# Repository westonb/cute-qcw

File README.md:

# cute-qcw
A compact qcw tesla coil system with a FPGA based controller. System design and construction are in progress. Build photos viewable here: https://www.flickr.com/photos/63341195@N08/sets/72157678478822788/

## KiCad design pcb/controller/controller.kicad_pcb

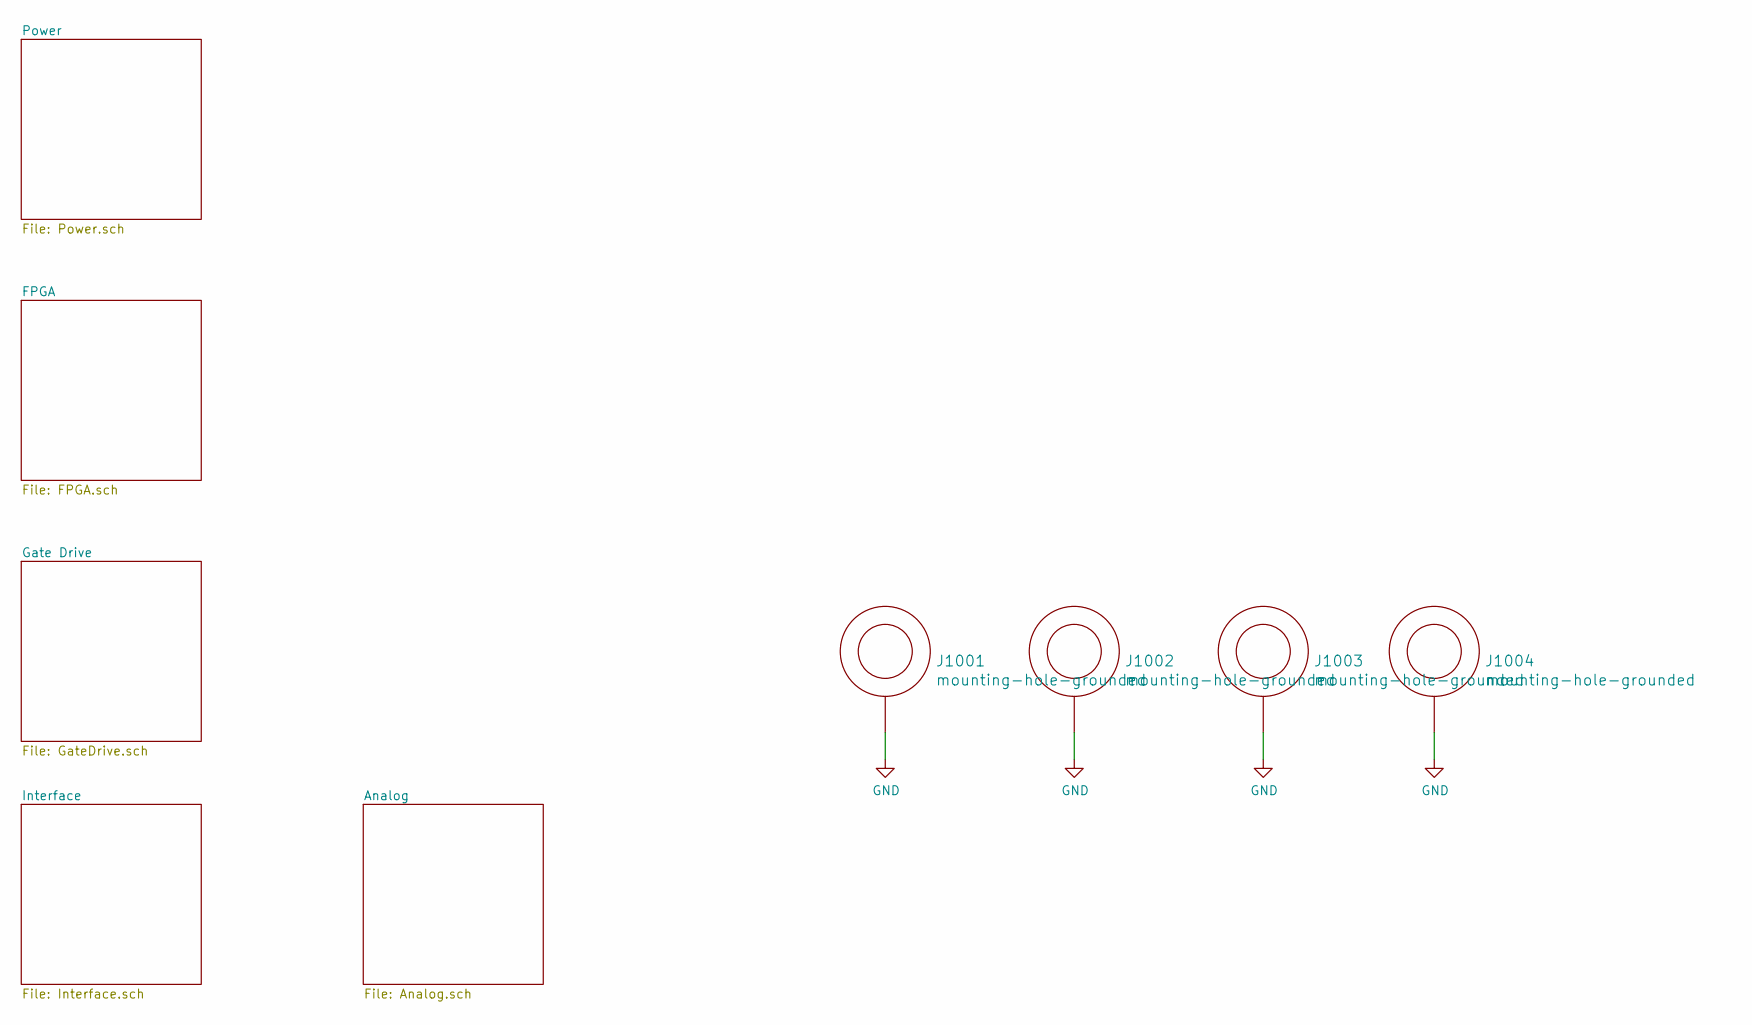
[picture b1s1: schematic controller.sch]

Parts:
J1001, J1002, J1003, J1004: mounting-hole-grounded; M3-tight-fit-pan-head

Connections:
GND: J1001.1, J1002.1, J1003.1, J1004.1; also elsewhere on the board

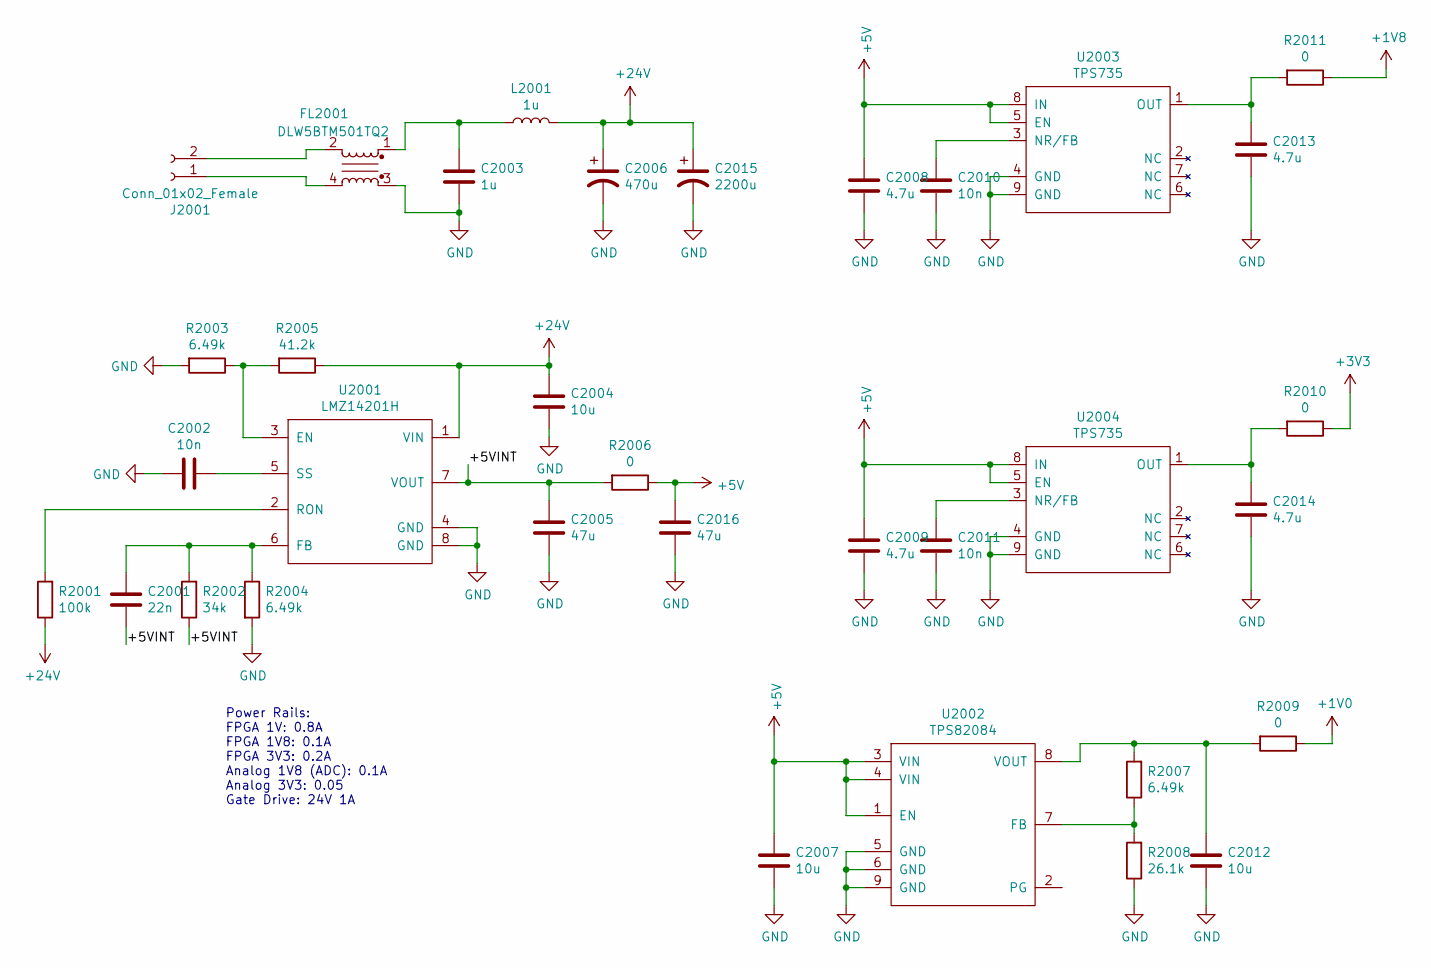
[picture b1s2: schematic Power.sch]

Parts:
C2001: 22n; C_0402_1005Metric
C2002, C2010, C2011: 10n; C_0402_1005Metric
C2003: 1u; C_0805_2012Metric
C2004: 10u; C_1206_3216Metric
C2005, C2016: 47u; C_0805_2012Metric
C2006: 470u; CP_Radial_D10.0mm_P5.00mm
C2007, C2012: 10u; C_0805_2012Metric
C2008, C2009, C2013, C2014: 4.7u; C_0402_1005Metric
C2015: 2200u; CAP_16mmx37mm_horizontal
FL2001: DLW5BTM501TQ2; DLW5BTM
J2001: Conn_01x02_Female; Terminal-block-plug_2x1_3.5mm-pitch
L2001: 1u; L_Vishay_IHLP-1212
R2001: 100k; R_0402_1005Metric
R2002: 34k; R_0402_1005Metric
R2003, R2004, R2007: 6.49k; R_0402_1005Metric
R2005: 41.2k; R_0402_1005Metric
R2006, R2009, R2010, R2011: 0; R_0805_2012Metric
R2008: 26.1k; R_0402_1005Metric
U2001: LMZ14201H; TO-PMOD-7
U2002: TPS82084; uSil-8
U2003, U2004: TPS735; SON-8_EP

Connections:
+1V0: R2009.1; also elsewhere on the board
+1V8: R2011.1; also elsewhere on the board
+3V3: R2010.1; also elsewhere on the board
+5V: C2007.1, C2008.2, C2009.2, C2016.1, R2006.1, U2002.1 (EN), U2002.3 (VIN), U2002.4 (VIN), U2003.5 (EN), U2003.8 (IN), U2004.5 (EN), U2004.8 (IN); also elsewhere on the board
+24V: C2004.1, C2006.1, C2015.1, L2001.2, R2001.1, R2005.1, U2001.1 (VIN); also elsewhere on the board
/Power/+5VINT: C2001.1, C2005.1, R2002.1, R2006.2, U2001.7 (VOUT)
GND: C2002.2, C2003.2, C2004.2, C2005.2, C2006.2, C2007.2, C2008.1, C2009.1, C2010.1, C2011.1, C2012.2, C2013.1, C2014.1, C2015.2, C2016.2, FL2001.3, R2003.2, R2004.2, R2008.1, U2001.4 (GND), U2001.8 (GND), U2002.5 (GND), U2002.6 (GND), U2002.9 (GND), U2003.4 (GND), U2003.9 (GND), U2004.4 (GND), U2004.9 (GND); also elsewhere on the board
unnamed: C2001.2, R2002.2, R2004.1, U2001.6 (FB)
unnamed: C2002.1, U2001.5 (SS)
unnamed: C2003.1, FL2001.1, L2001.1
unnamed: C2010.2, U2003.3 (NR/FB)
unnamed: C2011.2, U2004.3 (NR/FB)
unnamed: C2012.1, R2007.2, R2009.2, U2002.8 (VOUT)
unnamed: C2013.2, R2011.2, U2003.1 (OUT)
unnamed: C2014.2, R2010.2, U2004.1 (OUT)
unnamed: FL2001.2, J2001.2
unnamed: FL2001.4, J2001.1
unnamed: R2001.2, U2001.2 (RON)
unnamed: R2003.1, R2005.2, U2001.3 (EN)
unnamed: R2007.1, R2008.2, U2002.7 (FB)

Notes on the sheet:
Power Rails: FPGA 1V: 0.8A FPGA 1V8: 0.1A FPGA 3V3: 0.2A Analog 1V8 (ADC): 0.1A Analog 3V3: 0.05 Gate Drive: 24V 1A

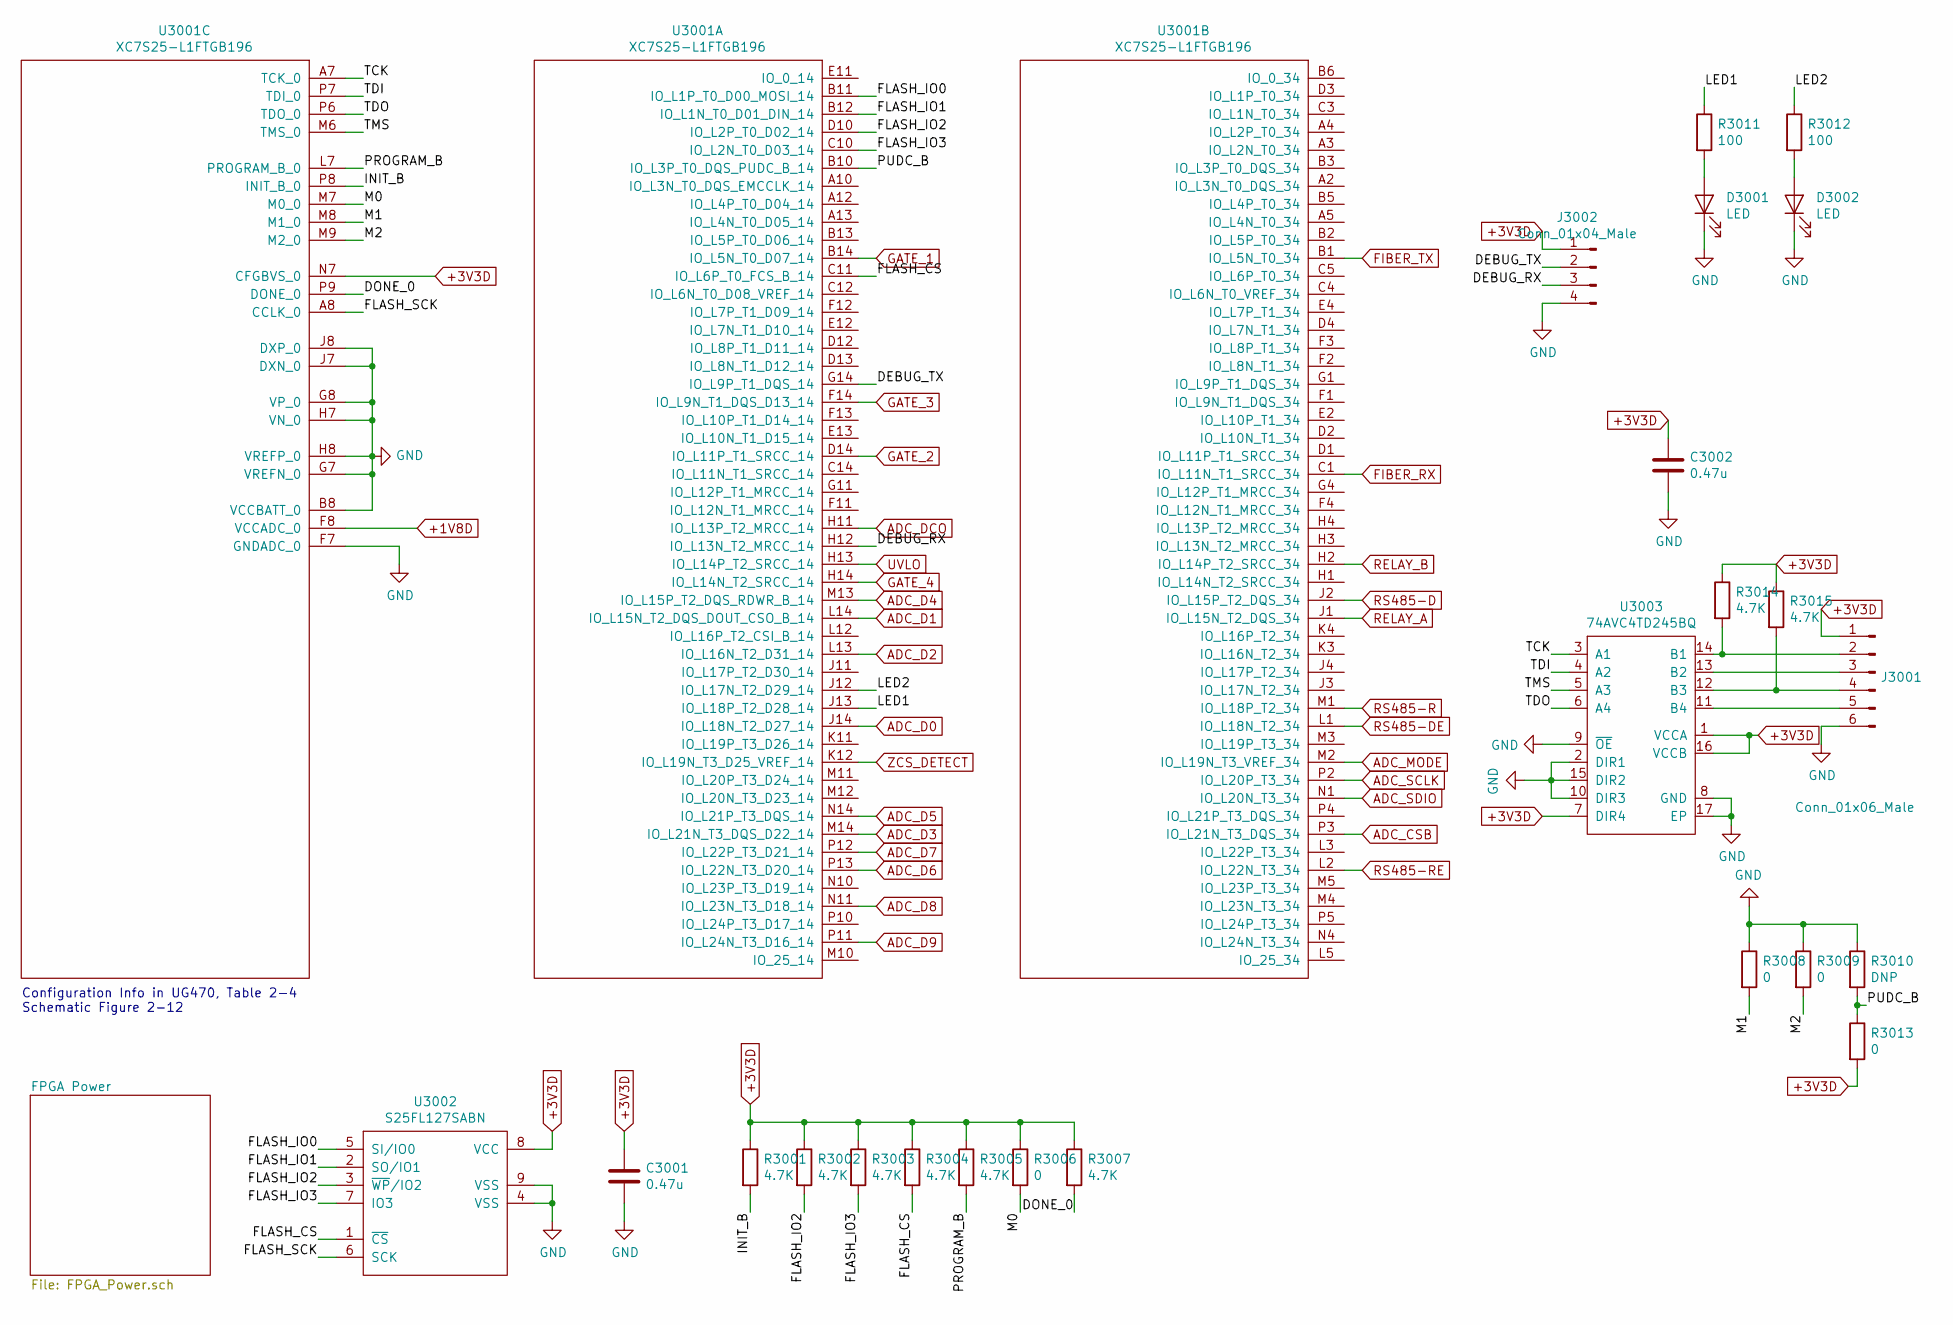
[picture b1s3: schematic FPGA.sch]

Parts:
C3001, C3002: 0.47u; C_0402_1005Metric
D3001, D3002: LED; LED-T1-RIGHT-ANGLE_4.6x4.4mm
J3001: Conn_01x06_Male; PinHeader_1x06_P2.54mm_Vertical
J3002: Conn_01x04_Male; PinHeader_1x04_P2.54mm_Vertical
R3001, R3002, R3003, R3004, R3005, R3007, R3014, R3015: 4.7K; R_0402_1005Metric
R3006, R3008, R3009, R3013: 0; R_0402_1005Metric
R3010: DNP; R_0402_1005Metric
R3011, R3012: 100; R_0402_1005Metric
U3001: XC7S25-L1FTGB196; FTGB196
U3002: S25FL127SABN; WSON-8-1EP_6x5mm_P1.27mm_EP3.4x4mm
U3003: 74AVC4TD245BQ; DHVQFN16

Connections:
+1V8D: U3001.F8 (VCCADC_0); also elsewhere on the board
+3V3D: C3001.1, C3002.1, J3001.1, J3002.1, R3001.1, R3002.1, R3003.1, R3004.1, R3005.1, R3006.1, R3007.1, R3013.2, R3014.1, R3015.1, U3001.N7 (CFGBVS_0), U3002.8 (VCC), U3003.1 (VCCA), U3003.7 (DIR4), U3003.16 (VCCB); also elsewhere on the board
/FPGA/DEBUG_RX: J3002.3, U3001.H12 (IO_L13N_T2_MRCC_14)
/FPGA/DEBUG_TX: J3002.2, U3001.G14 (IO_L9P_T1_DQS_14)
/FPGA/DONE_0: R3007.2, U3001.P9 (DONE_0)
/FPGA/FLASH_CS: R3004.2, U3001.C11 (IO_L6P_T0_FCS_B_14), U3002.1 (~CS)
/FPGA/FLASH_IO0: U3001.B11 (IO_L1P_T0_D00_MOSI_14), U3002.5 (SI/IO0)
/FPGA/FLASH_IO1: U3001.B12 (IO_L1N_T0_D01_DIN_14), U3002.2 (SO/IO1)
/FPGA/FLASH_IO2: R3002.2, U3001.D10 (IO_L2P_T0_D02_14), U3002.3 (~WP~/IO2)
/FPGA/FLASH_IO3: R3003.2, U3001.C10 (IO_L2N_T0_D03_14), U3002.7 (IO3)
/FPGA/FLASH_SCK: U3001.A8 (CCLK_0), U3002.6 (SCK)
/FPGA/INIT_B: R3001.2, U3001.P8 (INIT_B_0)
/FPGA/LED1: R3011.1, U3001.J13 (IO_L18P_T2_D28_14)
/FPGA/LED2: R3012.1, U3001.J12 (IO_L17N_T2_D29_14)
/FPGA/M0: R3006.2, U3001.M7 (M0_0)
/FPGA/M1: R3008.2, U3001.M8 (M1_0)
/FPGA/M2: R3009.2, U3001.M9 (M2_0)
/FPGA/PROGRAM_B: R3005.2, U3001.L7 (PROGRAM_B_0)
/FPGA/PUDC_B: R3010.2, R3013.1, U3001.B10 (IO_L3P_T0_DQS_PUDC_B_14)
/FPGA/TCK: U3001.A7 (TCK_0), U3003.3 (A1)
/FPGA/TDI: U3001.P7 (TDI_0), U3003.4 (A2)
/FPGA/TDO: U3001.P6 (TDO_0), U3003.6 (A4)
/FPGA/TMS: U3001.M6 (TMS_0), U3003.5 (A3)
ADC_CSB: U3001.P3 (IO_L21N_T3_DQS_34); also elsewhere on the board
ADC_D0: U3001.J14 (IO_L18N_T2_D27_14); also elsewhere on the board
ADC_D1: U3001.L14 (IO_L15N_T2_DQS_DOUT_CSO_B_14); also elsewhere on the board
ADC_D2: U3001.L13 (IO_L16N_T2_D31_14); also elsewhere on the board
ADC_D3: U3001.M14 (IO_L21N_T3_DQS_D22_14); also elsewhere on the board
ADC_D4: U3001.M13 (IO_L15P_T2_DQS_RDWR_B_14); also elsewhere on the board
ADC_D5: U3001.N14 (IO_L21P_T3_DQS_14); also elsewhere on the board
ADC_D6: U3001.P13 (IO_L22N_T3_D20_14); also elsewhere on the board
ADC_D7: U3001.P12 (IO_L22P_T3_D21_14); also elsewhere on the board
ADC_D8: U3001.N11 (IO_L23N_T3_D18_14); also elsewhere on the board
ADC_D9: U3001.P11 (IO_L24N_T3_D16_14); also elsewhere on the board
ADC_DCO: U3001.H11 (IO_L13P_T2_MRCC_14); also elsewhere on the board
ADC_MODE: U3001.M2 (IO_L19N_T3_VREF_34); also elsewhere on the board
ADC_SCLK: U3001.P2 (IO_L20P_T3_34); also elsewhere on the board
ADC_SDIO: U3001.N1 (IO_L20N_T3_34); also elsewhere on the board
FIBER_RX: U3001.C1 (IO_L11N_T1_SRCC_34); also elsewhere on the board
FIBER_TX: U3001.B1 (IO_L5N_T0_34); also elsewhere on the board
GATE_1: U3001.B14 (IO_L5N_T0_D07_14); also elsewhere on the board
GATE_2: U3001.D14 (IO_L11P_T1_SRCC_14); also elsewhere on the board
GATE_3: U3001.F14 (IO_L9N_T1_DQS_D13_14); also elsewhere on the board
GATE_4: U3001.H14 (IO_L14N_T2_SRCC_14); also elsewhere on the board
GND: C3001.2, C3002.2, D3001.1 (K), D3002.1 (K), J3001.6, J3002.4, R3008.1, R3009.1, R3010.1, U3001.B8 (VCCBATT_0), U3001.F7 (GNDADC_0), U3001.G7 (VREFN_0), U3001.G8 (VP_0), U3001.H7 (VN_0), U3001.H8 (VREFP_0), U3001.J7 (DXN_0), U3001.J8 (DXP_0), U3002.4 (VSS), U3002.9 (VSS), U3003.2 (DIR1), U3003.8 (GND), U3003.9 (~OE), U3003.10 (DIR3), U3003.15 (DIR2), U3003.17 (EP); also elsewhere on the board
unnamed: D3001.2 (A), R3011.2
unnamed: D3002.2 (A), R3012.2
unnamed: J3001.2, R3014.2, U3003.14 (B1)
unnamed: J3001.3, U3003.13 (B2)
unnamed: J3001.4, R3015.2, U3003.12 (B3)
unnamed: J3001.5, U3003.11 (B4)
RELAY_A: U3001.J1 (IO_L15N_T2_DQS_34); also elsewhere on the board
RELAY_B: U3001.H2 (IO_L14P_T2_SRCC_34); also elsewhere on the board
RS485-D: U3001.J2 (IO_L15P_T2_DQS_34); also elsewhere on the board
RS485-DE: U3001.L1 (IO_L18N_T2_34); also elsewhere on the board
RS485-R: U3001.M1 (IO_L18P_T2_34); also elsewhere on the board
RS485-RE: U3001.L2 (IO_L22N_T3_34); also elsewhere on the board
UVLO: U3001.H13 (IO_L14P_T2_SRCC_14); also elsewhere on the board
ZCS_DETECT: U3001.K12 (IO_L19N_T3_D25_VREF_14); also elsewhere on the board

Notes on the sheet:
Configuration Info in UG470, Table 2-4 Schematic Figure 2-12

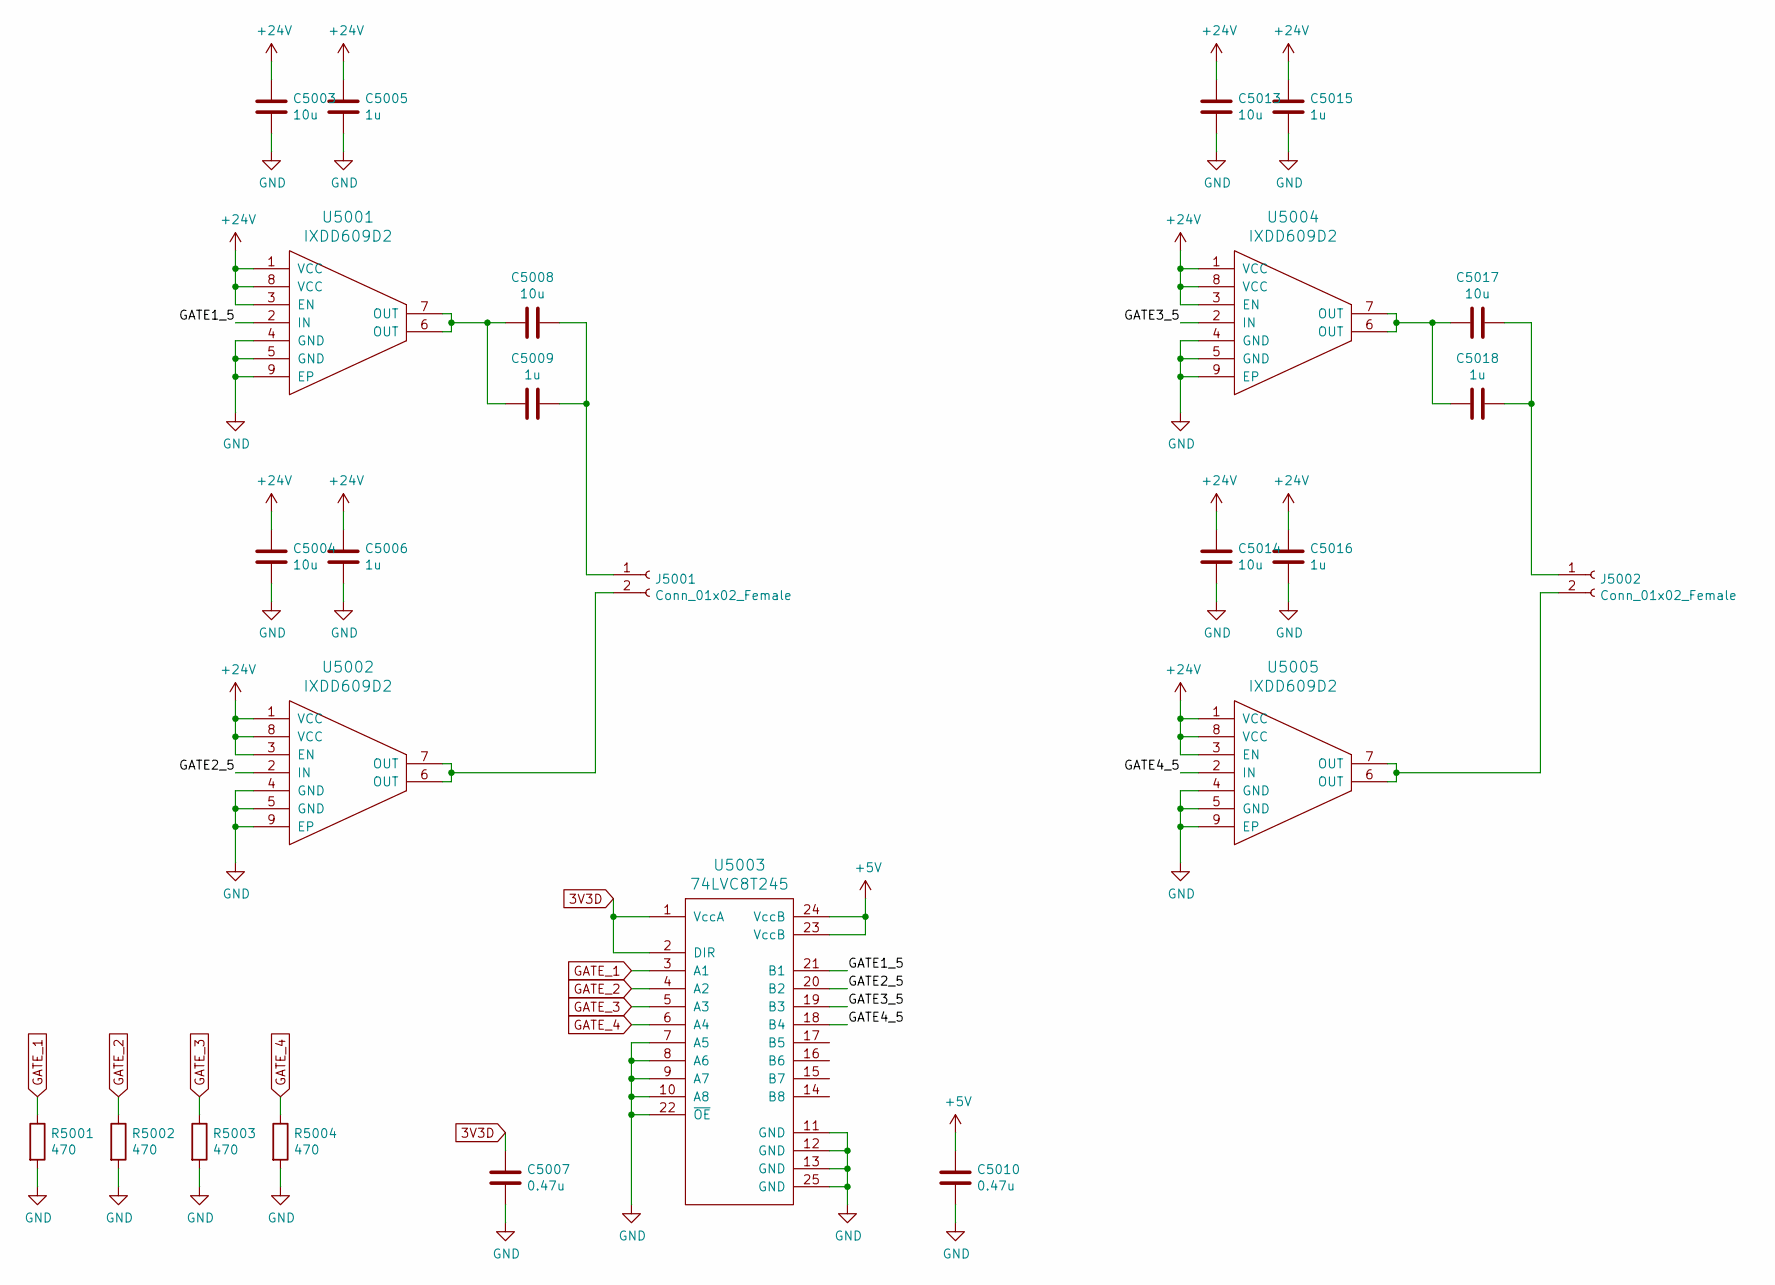
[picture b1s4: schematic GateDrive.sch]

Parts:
C5003, C5004, C5013, C5014, C5017: 10u; C_1206_3216Metric
C5005, C5006, C5009, C5015, C5016: 1u; C_0805_2012Metric
C5007, C5010: 0.47u; C_0402_1005Metric
C5008: 10u; C_0805_2012Metric
C5018: 1u; C_1206_3216Metric
J5001, J5002: Conn_01x02_Female; Terminal-block-plug_2x1_3.5mm-pitch
R5001, R5002, R5003, R5004: 470; R_0402_1005Metric
U5001, U5002, U5004, U5005: IXDD609D2; DFN-8_5x4mm_P0.95mm
U5003: 74LVC8T245; DHVQFN24_3.5x5.5mm_P0.5mm

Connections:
3V3D: C5007.1, U5003.1 (VccA), U5003.2 (DIR)
+5V: C5010.1, U5003.23 (VccB), U5003.24 (VccB); also elsewhere on the board
+24V: C5003.1, C5004.1, C5005.1, C5006.1, C5013.1, C5014.1, C5015.1, C5016.1, U5001.1 (VCC), U5001.3 (EN), U5001.8 (VCC), U5002.1 (VCC), U5002.3 (EN), U5002.8 (VCC), U5004.1 (VCC), U5004.3 (EN), U5004.8 (VCC), U5005.1 (VCC), U5005.3 (EN), U5005.8 (VCC); also elsewhere on the board
/Gate Drive/GATE1_5: U5001.2 (IN), U5003.21 (B1)
/Gate Drive/GATE2_5: U5002.2 (IN), U5003.20 (B2)
/Gate Drive/GATE3_5: U5003.19 (B3), U5004.2 (IN)
/Gate Drive/GATE4_5: U5003.18 (B4), U5005.2 (IN)
GATE_1: R5001.1, U5003.3 (A1); also elsewhere on the board
GATE_2: R5002.1, U5003.4 (A2); also elsewhere on the board
GATE_3: R5003.1, U5003.5 (A3); also elsewhere on the board
GATE_4: R5004.1, U5003.6 (A4); also elsewhere on the board
GND: C5003.2, C5004.2, C5005.2, C5006.2, C5007.2, C5010.2, C5013.2, C5014.2, C5015.2, C5016.2, R5001.2, R5002.2, R5003.2, R5004.2, U5001.4 (GND), U5001.5 (GND), U5001.9 (EP), U5002.4 (GND), U5002.5 (GND), U5002.9 (EP), U5003.7 (A5), U5003.8 (A6), U5003.9 (A7), U5003.10 (A8), U5003.11 (GND), U5003.12 (GND), U5003.13 (GND), U5003.22 (~OE), U5003.25 (GND), U5004.4 (GND), U5004.5 (GND), U5004.9 (EP), U5005.4 (GND), U5005.5 (GND), U5005.9 (EP); also elsewhere on the board
unnamed: C5008.1, C5009.1, J5001.1
unnamed: C5008.2, C5009.2, U5001.6 (OUT), U5001.7 (OUT)
unnamed: C5017.1, C5018.1, J5002.1
unnamed: C5017.2, C5018.2, U5004.6 (OUT), U5004.7 (OUT)
unnamed: J5001.2, U5002.6 (OUT), U5002.7 (OUT)
unnamed: J5002.2, U5005.6 (OUT), U5005.7 (OUT)

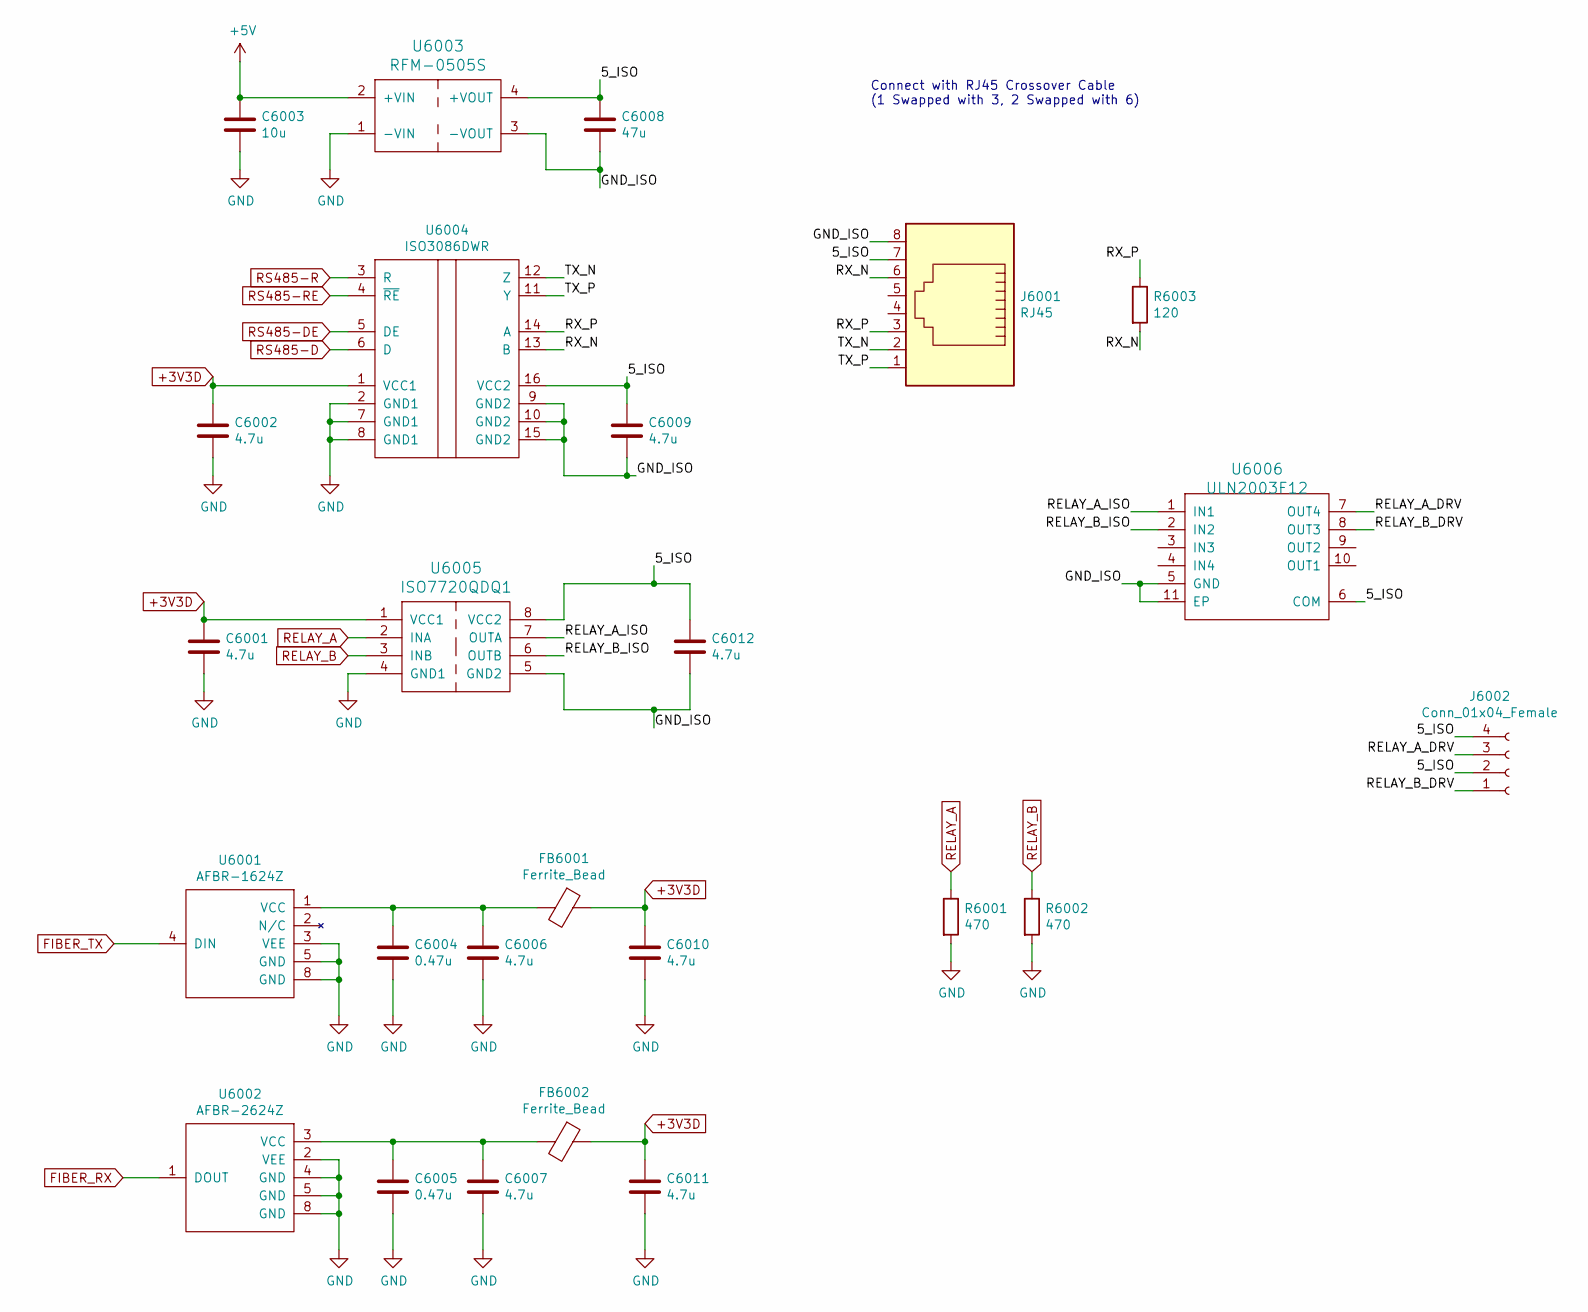
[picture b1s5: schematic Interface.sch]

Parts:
C6001, C6002, C6006, C6007, C6009, C6010, C6011, C6012: 4.7u; C_0402_1005Metric
C6003: 10u; C_0805_2012Metric
C6004, C6005: 0.47u; C_0402_1005Metric
C6008: 47u; C_0805_2012Metric
FB6001, FB6002: Ferrite_Bead; L_0805_2012Metric
J6001: RJ45; RJ45_Amphenol_54602-x08_Horizontal
J6002: Conn_01x04_Female; Terminal-block-plug_4x1_3.5mm-pitch
R6001, R6002: 470; R_0402_1005Metric
R6003: 120; R_1206_3216Metric
U6001: AFBR-1624Z; versatile-link_horizontal
U6002: AFBR-2624Z; versatile-link_horizontal
U6003: RFM-0505S
U6004: ISO3086DWR; SOIC-16W_7.5x10.3mm_P1.27mm
U6005: ISO7720QDQ1; SOIC-8_3.9x4.9mm_P1.27mm
U6006: ULN2003F12; DFN-10-1EP_3x3mm_P0.5mm_EP1.55x2.48mm

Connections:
+3V3D: C6001.1, C6002.1, C6010.1, C6011.1, FB6001.1, FB6002.1, U6004.1 (VCC1), U6005.1 (VCC1); also elsewhere on the board
+5V: C6003.1, U6003.2 (+VIN); also elsewhere on the board
/Interface/5_ISO: C6008.1, C6009.1, C6012.1, J6001.7, J6002.2, J6002.4, U6003.4 (+VOUT), U6004.16 (VCC2), U6005.8 (VCC2), U6006.6 (COM)
/Interface/GND_ISO: C6008.2, C6009.2, C6012.2, J6001.8, U6003.3 (-VOUT), U6004.9 (GND2), U6004.10 (GND2), U6004.15 (GND2), U6005.5 (GND2), U6006.5 (GND), U6006.11 (EP)
/Interface/RELAY_A_DRV: J6002.3, U6006.7 (OUT4)
/Interface/RELAY_A_ISO: U6005.7 (OUTA), U6006.1 (IN1)
/Interface/RELAY_B_DRV: J6002.1, U6006.8 (OUT3)
/Interface/RELAY_B_ISO: U6005.6 (OUTB), U6006.2 (IN2)
/Interface/RX_N: J6001.6, R6003.2, U6004.13 (B)
/Interface/RX_P: J6001.3, R6003.1, U6004.14 (A)
/Interface/TX_N: J6001.2, U6004.12 (Z)
/Interface/TX_P: J6001.1, U6004.11 (Y)
FIBER_RX: U6002.1 (DOUT); also elsewhere on the board
FIBER_TX: U6001.4 (DIN); also elsewhere on the board
GND: C6001.2, C6002.2, C6003.2, C6004.2, C6005.2, C6006.2, C6007.2, C6010.2, C6011.2, R6001.2, R6002.2, U6001.3 (VEE), U6001.5 (GND), U6001.8 (GND), U6002.2 (VEE), U6002.4 (GND), U6002.5 (GND), U6002.8 (GND), U6003.1 (-VIN), U6004.2 (GND1), U6004.7 (GND1), U6004.8 (GND1), U6005.4 (GND1); also elsewhere on the board
unnamed: C6004.1, C6006.1, FB6001.2, U6001.1 (VCC)
unnamed: C6005.1, C6007.1, FB6002.2, U6002.3 (VCC)
RELAY_A: R6001.1, U6005.2 (INA); also elsewhere on the board
RELAY_B: R6002.1, U6005.3 (INB); also elsewhere on the board
RS485-D: U6004.6 (D); also elsewhere on the board
RS485-DE: U6004.5 (DE); also elsewhere on the board
RS485-R: U6004.3 (R); also elsewhere on the board
RS485-RE: U6004.4 (~RE); also elsewhere on the board

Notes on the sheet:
Connect with RJ45 Crossover Cable (1 Swapped with 3, 2 Swapped with 6)

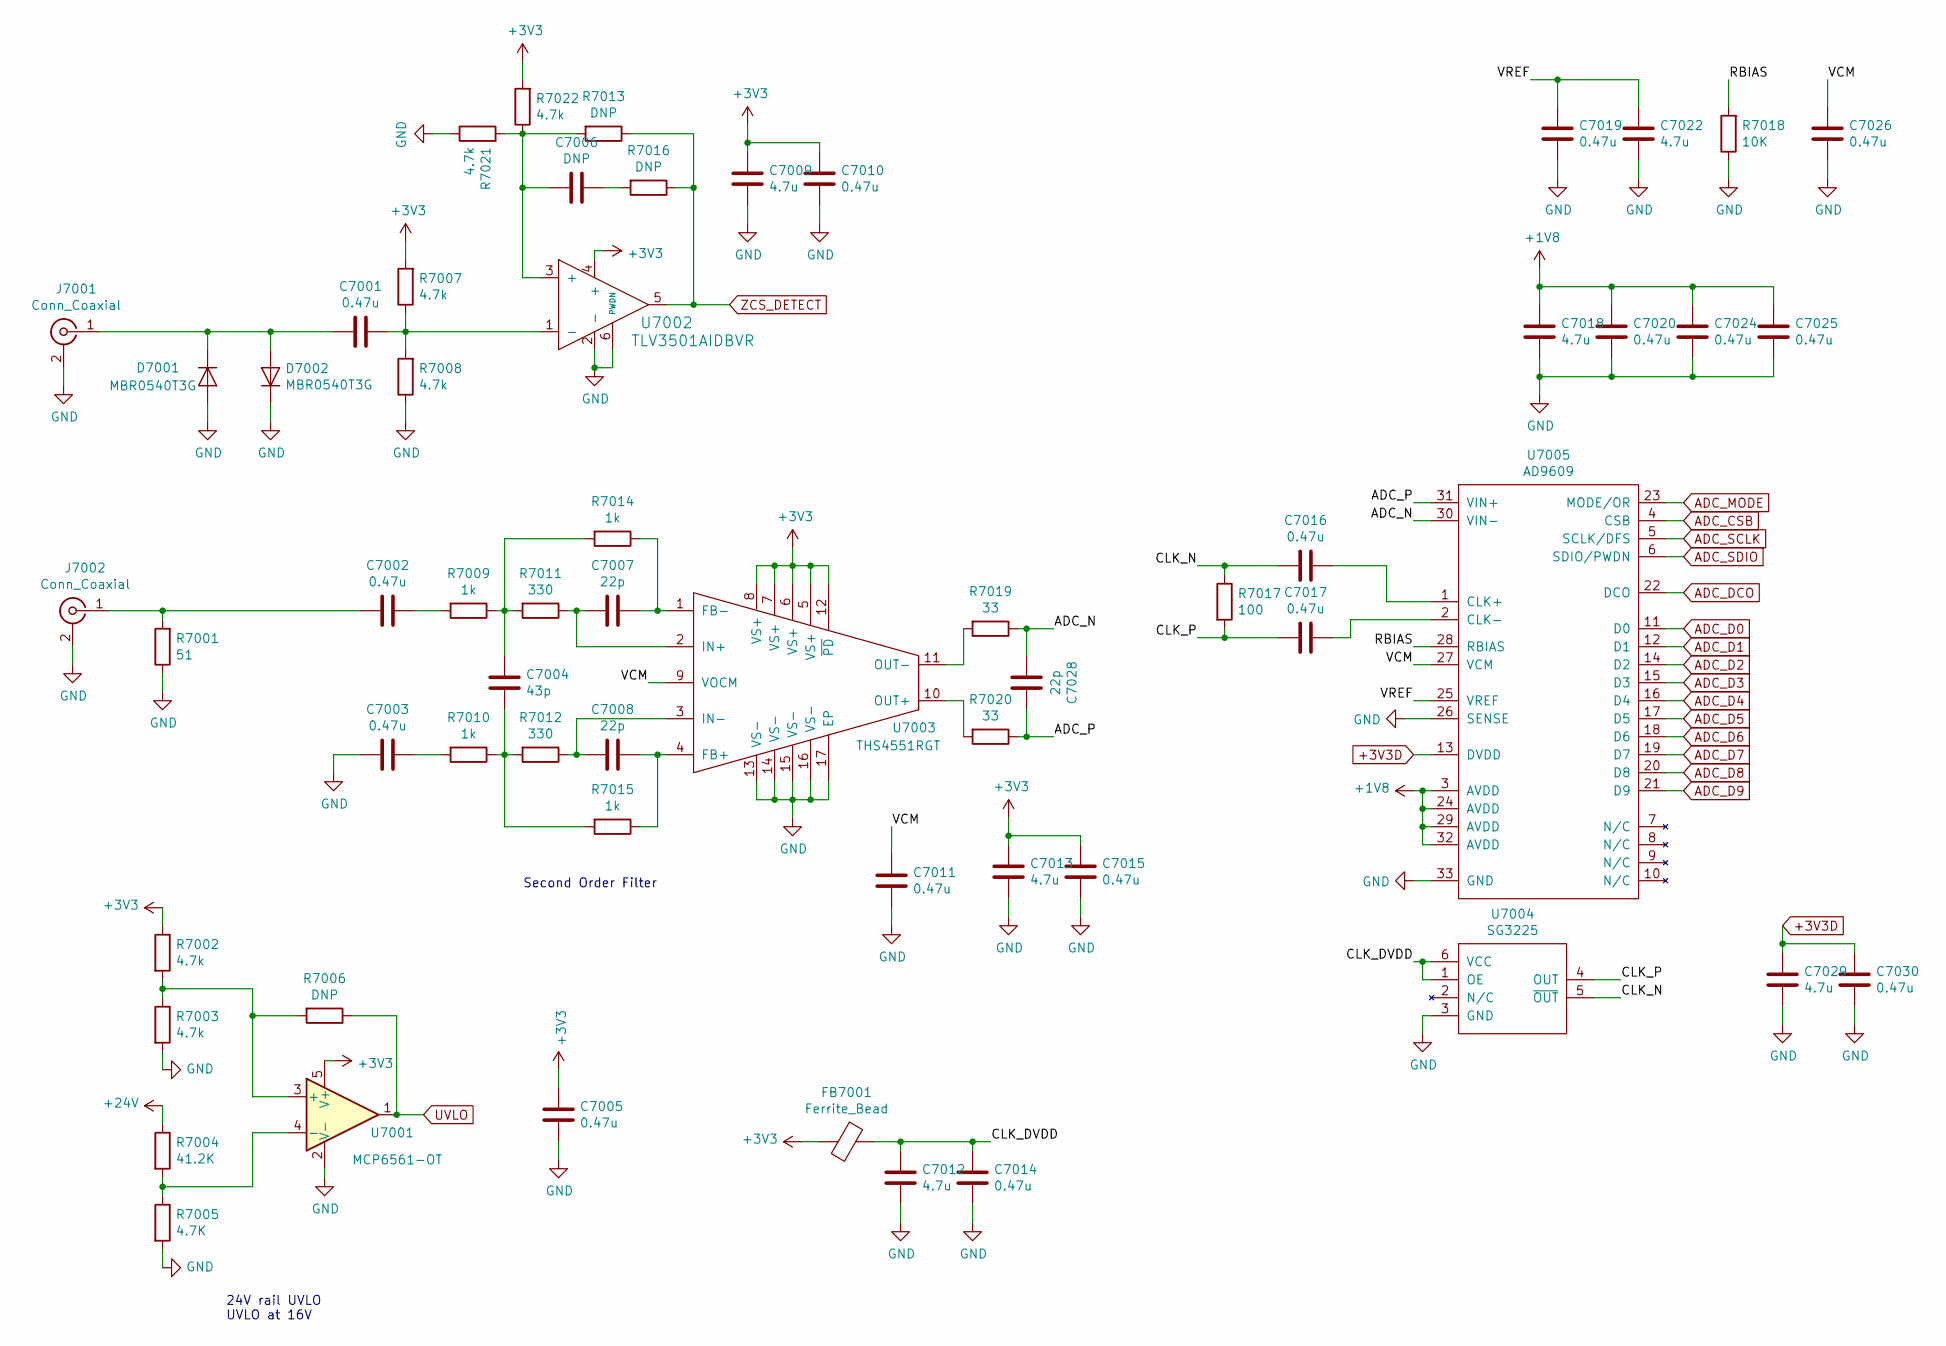
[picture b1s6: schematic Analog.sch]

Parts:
C7001, C7002, C7003, C7005, C7010, C7011, C7014, C7015, C7016, C7017, C7019, C7020, C7024, C7025, C7026, C7030: 0.47u; C_0402_1005Metric
C7004: 43p; C_0402_1005Metric
C7006: DNP; C_0402_1005Metric
C7007, C7008, C7028: 22p; C_0402_1005Metric
C7009, C7012, C7013, C7018, C7022, C7029: 4.7u; C_0402_1005Metric
D7001, D7002: MBR0540T3G; D_SOD-123
FB7001: Ferrite_Bead; L_0805_2012Metric
J7001, J7002: Conn_Coaxial; SMA_Amphenol_132134-16_Vertical
R7001: 51; R_2512_6332Metric
R7002, R7003, R7007, R7008, R7021, R7022: 4.7k; R_0402_1005Metric
R7004: 41.2K; R_0402_1005Metric
R7005: 4.7K; R_0402_1005Metric
R7006, R7013, R7016: DNP; R_0402_1005Metric
R7009, R7010, R7014, R7015: 1k; R_0402_1005Metric
R7011, R7012: 330; R_0402_1005Metric
R7017: 100; R_0402_1005Metric
R7018: 10K; R_0402_1005Metric
R7019, R7020: 33; R_0402_1005Metric
U7001: MCP6561-OT; SOT-23-5
U7002: TLV3501AIDBVR; SOT-23-6
U7003: THS4551RGT; QFN-16-1EP_3x3mm_P0.5mm_EP1.8x1.8mm
U7004: SG3225
U7005: AD9609; QFN-32-1EP_5x5mm_P0.5mm_EP3.45x3.45mm

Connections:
+1V8: C7018.2, C7020.2, C7024.2, C7025.2, U7005.3 (AVDD), U7005.24 (AVDD), U7005.29 (AVDD), U7005.32 (AVDD); also elsewhere on the board
+3V3: C7005.1, C7009.2, C7010.2, C7013.2, C7015.2, FB7001.2, R7002.1, R7007.2, R7022.2, U7001.5 (V+), U7002.4 (+), U7003.5 (VS+), U7003.6 (VS+), U7003.7 (VS+), U7003.8 (VS+), U7003.12 (~PD); also elsewhere on the board
+3V3D: C7029.2, C7030.2, U7005.13 (DVDD); also elsewhere on the board
+24V: R7004.1; also elsewhere on the board
/Analog/ADC_N: C7028.2, R7019.1, U7005.30 (VIN-)
/Analog/ADC_P: C7028.1, R7020.1, U7005.31 (VIN+)
/Analog/CLK_DVDD: C7012.2, C7014.2, FB7001.1, U7004.1 (OE), U7004.6 (VCC)
/Analog/CLK_N: C7016.1, R7017.1, U7004.5 (~OUT)
/Analog/CLK_P: C7017.1, R7017.2, U7004.4 (OUT)
/Analog/RBIAS: R7018.2, U7005.28 (RBIAS)
/Analog/VCM: C7011.2, C7026.2, U7003.9 (VOCM), U7005.27 (VCM)
/Analog/VREF: C7019.2, C7022.2, U7005.25 (VREF)
ADC_CSB: U7005.4 (CSB); also elsewhere on the board
ADC_D0: U7005.11 (D0); also elsewhere on the board
ADC_D1: U7005.12 (D1); also elsewhere on the board
ADC_D2: U7005.14 (D2); also elsewhere on the board
ADC_D3: U7005.15 (D3); also elsewhere on the board
ADC_D4: U7005.16 (D4); also elsewhere on the board
ADC_D5: U7005.17 (D5); also elsewhere on the board
ADC_D6: U7005.18 (D6); also elsewhere on the board
ADC_D7: U7005.19 (D7); also elsewhere on the board
ADC_D8: U7005.20 (D8); also elsewhere on the board
ADC_D9: U7005.21 (D9); also elsewhere on the board
ADC_DCO: U7005.22 (DCO); also elsewhere on the board
ADC_MODE: U7005.23 (MODE/OR); also elsewhere on the board
ADC_SCLK: U7005.5 (SCLK/DFS); also elsewhere on the board
ADC_SDIO: U7005.6 (SDIO/PWDN); also elsewhere on the board
GND: C7003.2, C7005.2, C7009.1, C7010.1, C7011.1, C7012.1, C7013.1, C7014.1, C7015.1, C7018.1, C7019.1, C7020.1, C7022.1, C7024.1, C7025.1, C7026.1, C7029.1, C7030.1, D7001.2 (A), D7002.1 (K), J7001.2 (Ext), J7002.2 (Ext), R7001.1, R7003.2, R7005.2, R7008.1, R7018.1, R7021.1, U7001.2 (V-), U7002.2 (-), U7002.6 (PWDN), U7003.13 (VS-), U7003.14 (VS-), U7003.15 (VS-), U7003.16 (VS-), U7003.17 (EP), U7004.3 (GND), U7005.26 (SENSE), U7005.33 (GND); also elsewhere on the board
unnamed: C7001.1, R7007.1, R7008.2, U7002.1 (-)
unnamed: C7001.2, D7001.1 (K), D7002.2 (A), J7001.1 (In)
unnamed: C7002.1, R7009.2
unnamed: C7002.2, J7002.1 (In), R7001.2
unnamed: C7003.1, R7010.2
unnamed: C7004.1, R7010.1, R7012.2, R7015.2
unnamed: C7004.2, R7009.1, R7011.2, R7014.2
unnamed: C7006.1, R7016.2
unnamed: C7006.2, R7013.2, R7021.2, R7022.1, U7002.3 (+)
unnamed: C7007.1, R7014.1, U7003.1 (FB-)
unnamed: C7007.2, R7011.1, U7003.2 (IN+)
unnamed: C7008.1, R7015.1, U7003.4 (FB+)
unnamed: C7008.2, R7012.1, U7003.3 (IN-)
unnamed: C7016.2, U7005.1 (CLK+)
unnamed: C7017.2, U7005.2 (CLK-)
unnamed: R7002.2, R7003.1, R7006.2, U7001.3 (+)
unnamed: R7004.2, R7005.1, U7001.4 (-)
unnamed: R7019.2, U7003.11 (OUT-)
unnamed: R7020.2, U7003.10 (OUT+)
UVLO: R7006.1, U7001.1; also elsewhere on the board
ZCS_DETECT: R7013.1, R7016.1, U7002.5; also elsewhere on the board

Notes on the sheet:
24V rail UVLO UVLO at 16V
Second Order Filter
